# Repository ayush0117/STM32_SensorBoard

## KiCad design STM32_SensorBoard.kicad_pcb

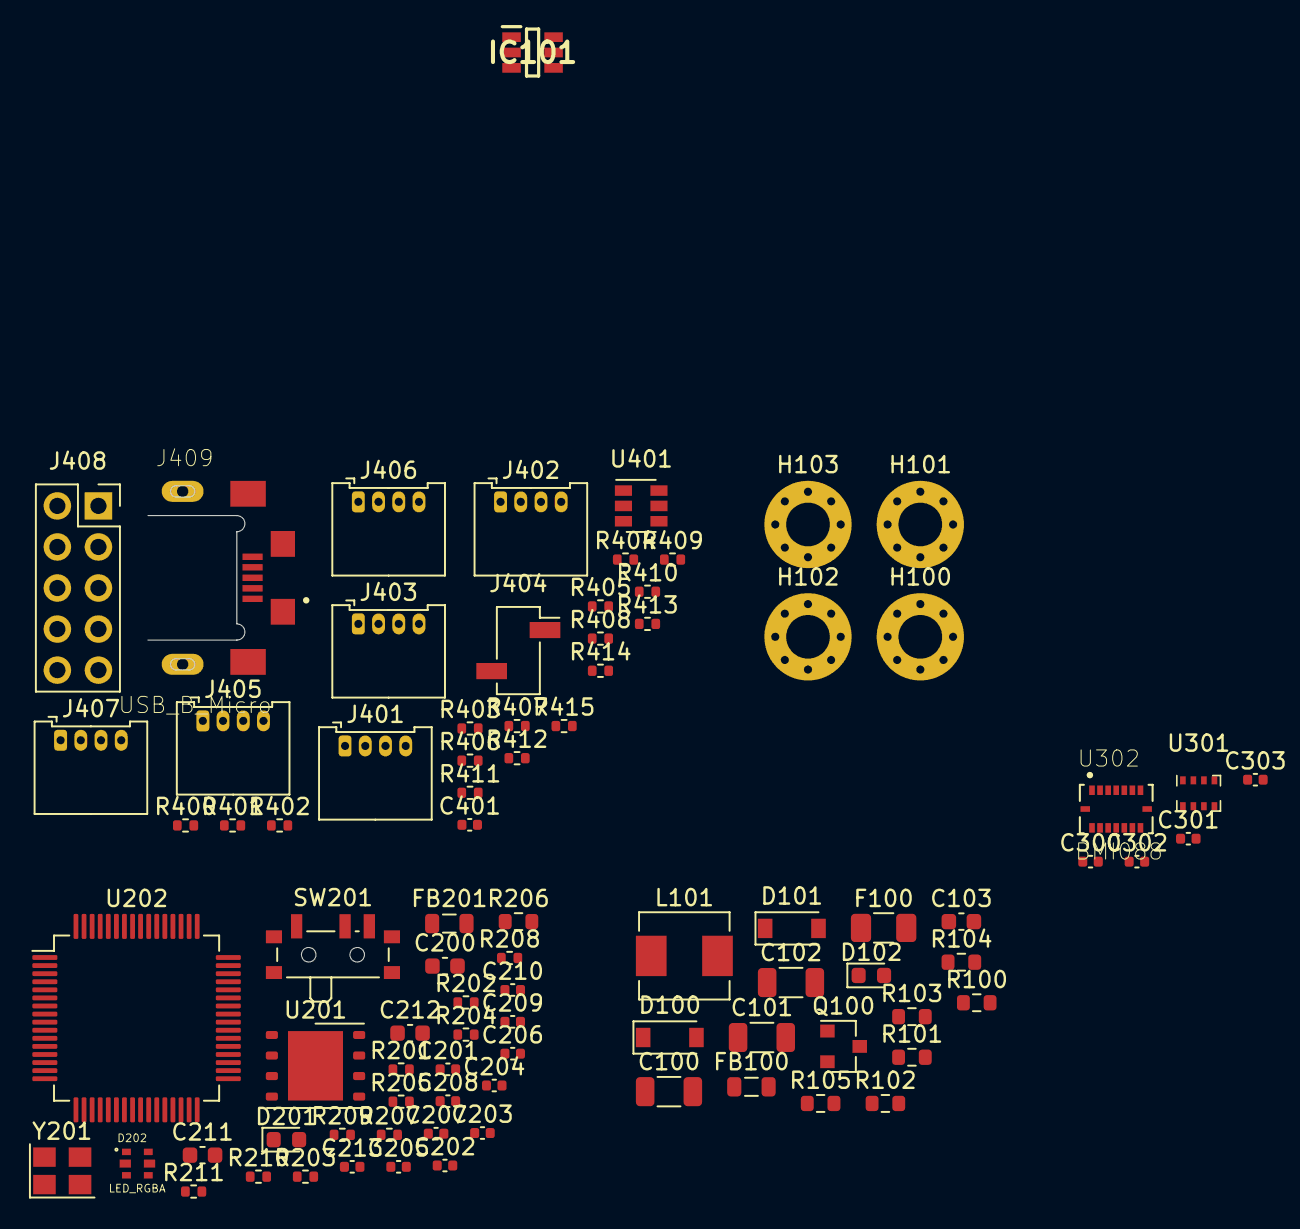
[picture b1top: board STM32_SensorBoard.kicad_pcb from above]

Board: 2 copper layers, 87 parts (0 on the bottom side), 82 nets, no tracks yet.

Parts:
C100, C101, C102: 10u; C_1206_3216Metric
C103: 10n; C_0603_1608Metric
C200: 4u7; C_0603_1608Metric
C201, C202, C203, C204, C205, C206, C213, C300, C301, C302, C303, C401: 100n; C_0402_1005Metric
C207: 1u; C_0402_1005Metric
C208: 10n; C_0402_1005Metric
C209, C210: 12p; C_0402_1005Metric
C211, C212: 2u2; C_0603_1608Metric
D100, D101: B5819W; D_SOD-123
D102: GREEN; LED_0603_1608Metric
D201: RED; LED_0603_1608Metric
D202: LED_RGBA; LED_19-337%2fR6GHBHC-A01%2f2T
F100: 250mA; Fuse_1206_3216Metric
FB100: 600 @ 600 MHz; L_0805_2012Metric
FB201: 600 @ 600 Hz; L_0805_2012Metric
H100, H101, H102, H103: MountingHole_Pad; MountingHole_2.7mm_Pad_Via
IC101: MP2359DJ-LF-Z; SOT95P280X100-6N
J401, J402, J403, J405, J406, J407: Conn_01x04; Molex_PicoBlade_53048-0410_1x04_P1.25mm_Horizontal
J404: Conn_01x02; PinSocket_1x02_P2.54mm_Vertical_SMD_Pin1Right
J408: Conn_02x05_Odd_Even; PinSocket_2x05_P2.54mm_Vertical
J409: USB_B_Micro; CUI_UJ2-MIBH-4-MSMT
L101: 10u; L_Sunlord_MWSA0518_5.4x5.2mm
Q100: AO3401A; SOT-23
R100: 100k; R_0603_1608Metric
R101: 68k; R_0603_1608Metric
R102: 47k; R_0603_1608Metric
R103: 15k; R_0603_1608Metric
R104: 1k5; R_0603_1608Metric
R105: 270; R_0603_1608Metric
R201, R202, R203, R205: 10k; R_0402_1005Metric
R204: 47; R_0402_1005Metric
R206: 1k; R_0603_1608Metric
R207: 1k; R_0402_1005Metric
R208, R209: 2k2; R_0402_1005Metric
R210, R211: 1K; R_0402_1005Metric
R400, R401, R402, R403, R404, R405, R406, R407, R408, R409, R410, R411, R412, R413, R414, R415: 22; R_0402_1005Metric
SW201: SW_SPDT; SW_SPDT_PCM12
U201: W25Q32JVZP; WSON-8-1EP_6x5mm_P1.27mm_EP3.4x4.3mm
U202: STM32F405RGTx; LQFP-64_10x10mm_P0.5mm
U301: BMP280; Bosch_LGA-8_2x2.5mm_P0.65mm_ClockwisePinNumbering
U302: BMI088; PQFN50P450X300X100-16N
U401: USBLC6-2SC6; SOT-23-6
Y201: 16Mhz; Crystal_SMD_3225-4Pin_3.2x2.5mm

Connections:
+3.3VA: C207.1, C208.1, FB201.1, U202.13
+3V3: C101.1, C102.1, C200.1, C201.1, C202.1, C203.1, C204.1, C205.1, C206.1, C213.1, C300.1, C301.1, C302.1, C303.1, D102.2, D202.4, FB201.2, J401.1, J402.1, J403.1, J405.1, J406.1, J407.1, J408.1, L101.2, R102.1, R201.1, R202.1, R208.2, R209.2, SW201.1, U201.8, U202.1, U202.19, U202.32, U202.48, U202.64, U301.6, U301.8, U302.3, U302.11
+5V: D100.2, J409.1, U401.5
ADC1_IN0: R401.2, U202.14
ADC1_IN1: R404.2, U202.15
ADC1_IN2: R408.2, U202.16
ADC1_IN3: R411.2, U202.17
BOOT0: R203.2, U202.60
BOOT1: R205.2, U202.28
BST: C103.1, IC101.1
FB: IC101.3, R102.2, R103.1
FLASH_!HOLD: R202.2, U201.7, U202.37
FLASH_!WP: R201.2, U201.3, U202.38
GND: C100.2, C101.2, C102.2, C200.2, C201.2, C202.2, C203.2, C204.2, C205.2, C206.2, C207.2, C208.2, C209.2, C210.2, C211.2, C212.2, C213.2, C300.2, C301.2, C302.2, C303.2, C401.2, D101.2, H100.1, H101.1, H102.1, H103.1, IC101.2, J401.4, J402.4, J403.4, J404.2, J405.4, J406.4, J407.4, J408.3, J408.5, J408.9, J409.5, Q100.1, R101.2, R104.2, R105.2, R205.1, R206.1, SW201.3, U201.4, U201.9, U202.12, U202.18, U202.63, U301.1, U301.7, U302.2, U302.4, U302.6, U302.7, U401.2, Y201.2, Y201.4
HSE_IN: C209.1, U202.5, Y201.1
HSE_OUT: R204.2, U202.6
I2C1_SCL: R208.1, R402.2, U202.61
I2C1_SDA: R209.1, R400.2, U202.62
INT_ACC: U202.10, U302.16
INT_GYR: U202.11, U302.12
NRST: C401.1, R415.1, U202.7
unnamed: C100.1, FB100.1, IC101.5, R100.1
unnamed: C210.1, R204.1, Y201.3
unnamed: C211.1, U202.31
unnamed: C212.1, U202.47
unnamed: D100.1, F100.1, Q100.2
unnamed: D102.1, R104.1
unnamed: D201.1, R206.2
unnamed: D201.2, R203.1, SW201.2
unnamed: D202.1, R207.1
unnamed: D202.2, R210.1
unnamed: D202.3, R211.1
unnamed: F100.2, FB100.2
unnamed: IC101.4, R100.2, R101.1
unnamed: J401.2, R401.1
unnamed: J401.3, R404.1
unnamed: J402.2, R402.1
unnamed: J402.3, R400.1
unnamed: J403.2, R403.1
unnamed: J403.3, R405.1
unnamed: J405.2, R406.1
unnamed: J405.3, R409.1
unnamed: J406.2, R407.1
unnamed: J406.3, R410.1
unnamed: J407.2, R408.1
unnamed: J407.3, R411.1
unnamed: J408.2, R412.2
unnamed: J408.4, R413.2
unnamed: J408.6, R414.2
unnamed: J408.10, R415.2
unnamed: R103.2, R105.1
SPI1_CS_ACC: U202.20, U302.14
SPI1_CS_GYR: U202.24, U302.5
SPI1_MISO: U202.22, U302.10, U302.15
SPI1_MOSI: U202.23, U302.9
SPI1_SCK: U202.21, U302.8
SPI2_CS: U201.1, U202.33
SPI2_MISO: U201.2, U202.35
SPI2_MOSI: U201.5, U202.36
SPI2_SCK: U201.6, U202.34
SPI3_CS: U202.50, U301.2
SPI3_MISO: U202.52, U301.5
SPI3_MOSI: U202.53, U301.3
SPI3_SCK: U202.51, U301.4
SW: C103.2, D101.1, IC101.6, L101.1
SWCLK: R413.1, U202.49
SWDIO: R412.1, U202.46
SWO: R414.1, U202.55
TIM2_CH3: R403.2, U202.29
TIM2_CH4: R405.2, U202.30
TIM3_CH1: R207.2, U202.56
TIM3_CH2: R210.2, U202.57
TIM3_CH3: R407.2, U202.26
TIM3_CH4: R410.2, U202.27
TIM4_CH1: R211.2, U202.58
USART1_RX: R409.2, U202.43
USART1_TX: R406.2, U202.42
USB_CONN_D+: J409.3, U401.3
USB_CONN_D-: J409.2, U401.1
USB_D+: U202.45, U401.4
USB_D-: U202.44, U401.6
VCC: J404.1, Q100.3
